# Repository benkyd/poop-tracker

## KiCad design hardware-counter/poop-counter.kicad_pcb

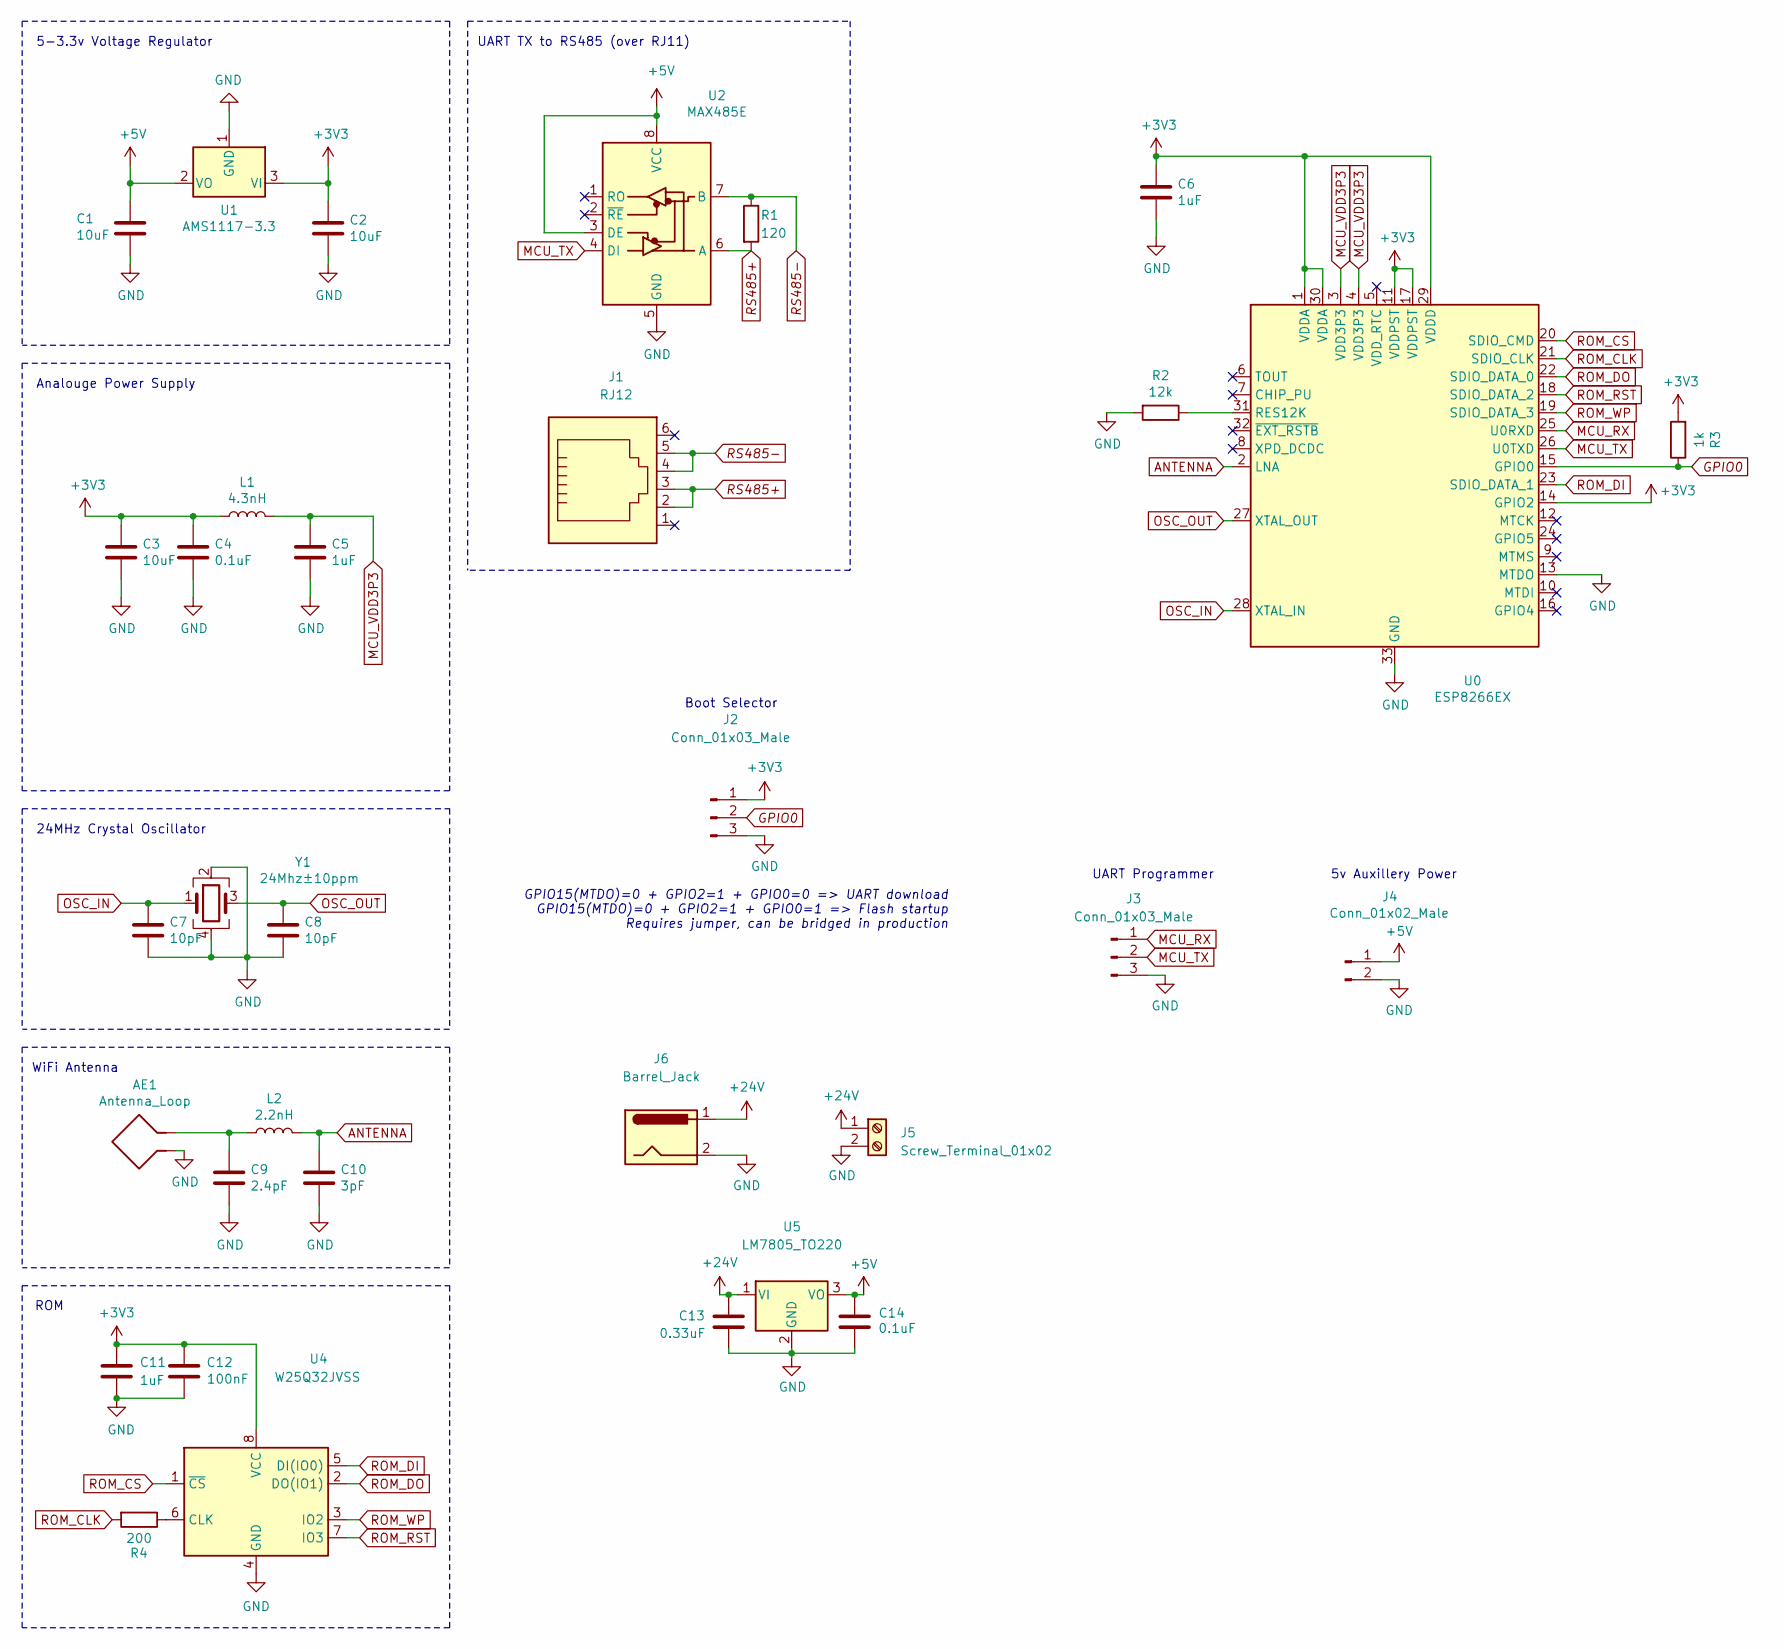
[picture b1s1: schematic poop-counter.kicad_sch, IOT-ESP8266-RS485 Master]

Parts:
AE1: Antenna_Loop; Texas_SWRA117D_2.4GHz_Right
C1, C2, C3: 10uF; C_0805_2012Metric_Pad1.18x1.45mm_HandSolder
C4, C14: 0.1uF; C_0805_2012Metric_Pad1.18x1.45mm_HandSolder
C5, C6, C11: 1uF; C_0805_2012Metric_Pad1.18x1.45mm_HandSolder
C7, C8: 10pF; C_0805_2012Metric_Pad1.18x1.45mm_HandSolder
C9: 2.4pF; C_0805_2012Metric_Pad1.18x1.45mm_HandSolder
C10: 3pF; C_0805_2012Metric_Pad1.18x1.45mm_HandSolder
C12: 100nF; C_0805_2012Metric_Pad1.18x1.45mm_HandSolder
C13: 0.33uF; C_0805_2012Metric_Pad1.18x1.45mm_HandSolder
J1: RJ12; RJ12_Amphenol_54601
J2, J3: Conn_01x03_Male; PinHeader_1x03_P2.54mm_Vertical
J4: Conn_01x02_Male; PinHeader_1x02_P2.54mm_Vertical
J5: Screw_Terminal_01x02; TerminalBlock_bornier-2_P5.08mm
J6: Barrel_Jack; BarrelJack_CLIFF_FC681465S_SMT_Horizontal
L1: 4.3nH; L_0805_2012Metric_Pad1.05x1.20mm_HandSolder
L2: 2.2nH; L_0805_2012Metric_Pad1.05x1.20mm_HandSolder
R1: 120; R_0805_2012Metric_Pad1.20x1.40mm_HandSolder
R2: 12k; R_0805_2012Metric_Pad1.20x1.40mm_HandSolder
R3: 1k; R_0805_2012Metric_Pad1.20x1.40mm_HandSolder
R4: 200; R_0805_2012Metric_Pad1.20x1.40mm_HandSolder
U0: ESP8266EX; QFN-32-1EP_5x5mm_P0.5mm_EP3.45x3.45mm
U1: AMS1117-3.3; SOT-223-3_TabPin2
U2: MAX485E; SOIC127P600X175-8N
U4: W25Q32JVSS; SOIC-8_5.23x5.23mm_P1.27mm
U5: LM7805_TO220; TO-220-3_Vertical
Y1: 24Mhz±10ppm; Crystal_SMD_EuroQuartz_X22-4Pin_2.5x2.0mm

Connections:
+3V3: C2.1, C3.1, C4.1, C6.1, C11.1, C12.1, J2.1, L1.1, R3.2, U0.1 (VDDA), U0.11 (VDDPST), U0.14 (GPIO2), U0.17 (VDDPST), U0.29 (VDDD), U0.30 (VDDA), U1.3 (VI), U4.8 (VCC)
+5V: C1.2, C14.1, J4.1, U1.2 (VO), U2.3 (DE), U2.8 (VCC), U5.3 (VO)
+24V: C13.2, J5.1, J6.1, U5.1 (VI)
ANTENNA: C10.1, L2.2, U0.2 (LNA)
GND: AE1.1, C1.1, C2.2, C3.2, C4.2, C5.2, C6.2, C7.2, C8.2, C9.2, C10.2, C11.2, C12.2, C13.1, C14.2, J2.3, J3.3, J4.2, J5.2, J6.2, R2.2, U0.13 (MTDO), U0.33 (GND), U1.1 (GND), U2.5 (GND), U4.4 (GND), U5.2 (GND), Y1.2, Y1.4
GPIO0: J2.2, R3.1, U0.15 (GPIO0)
MCU_RX: J3.1, U0.25 (U0RXD)
MCU_TX: J3.2, U0.26 (U0TXD), U2.4 (DI)
MCU_VDD3P3: C5.1, L1.2, U0.3 (VDD3P3), U0.4 (VDD3P3)
unnamed: AE1.2, C9.1, L2.1
unnamed: R2.1, U0.31 (RES12K)
unnamed: R4.1, U4.6 (CLK)
OSC_IN: C7.1, U0.28 (XTAL_IN), Y1.1
OSC_OUT: C8.1, U0.27 (XTAL_OUT), Y1.3
ROM_CLK: R4.2, U0.21 (SDIO_CLK)
ROM_CS: U0.20 (SDIO_CMD), U4.1 (~CS)
ROM_DI: U0.23 (SDIO_DATA_1), U4.5 (DI(IO0))
ROM_DO: U0.22 (SDIO_DATA_0), U4.2 (DO(IO1))
ROM_RST: U0.18 (SDIO_DATA_2), U4.7 (IO3)
ROM_WP: U0.19 (SDIO_DATA_3), U4.3 (IO2)
RS485+: J1.2, J1.3, R1.2, U2.6 (A)
RS485-: J1.4, J1.5, R1.1, U2.7 (B)
no_connect_23: J1.1
no_connect_24: J1.6
no_connect_25: U0.10 (MTDI)
no_connect_26: U0.12 (MTCK)
no_connect_27: U0.16 (GPIO4)
no_connect_28: U0.24 (GPIO5)
no_connect_29: U0.32 (~EXT_RSTB~)
no_connect_30: U0.5 (VDD_RTC)
no_connect_31: U0.6 (TOUT)
no_connect_32: U0.7 (CHIP_PU)
no_connect_33: U0.8 (XPD_DCDC)
no_connect_34: U0.9 (MTMS)
no_connect_35: U2.1 (RO)
no_connect_36: U2.2 (~RE)

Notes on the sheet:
WiFi Antenna
ROM
5-3.3v Voltage Regulator
Analouge Power Supply
24MHz Crystal Oscillator
UART TX to RS485 (over RJ11)
Boot Selector
GPIO15(MTDO)=0 + GPIO2=1 + GPIO0=0 => UART download GPIO15(MTDO)=0 + GPIO2=1 + GPIO0=1 => Flash startup Requires jumper, can be bridged in production
UART Programmer
5v Auxillery Power

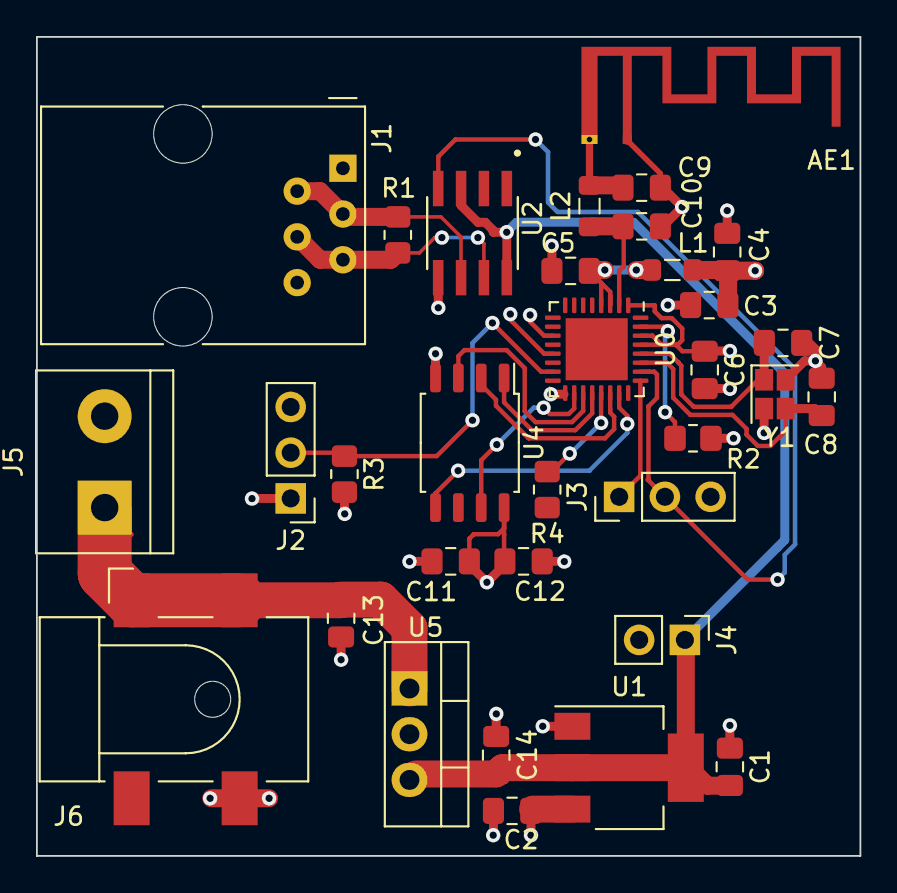
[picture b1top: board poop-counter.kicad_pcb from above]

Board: 4 copper layers, 45.8 x 45.5 mm, 33 parts (0 on the bottom side), 22 nets.

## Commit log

2021-07-18 started component gathering
2021-07-19 voltage regulation and decoupling for mcu
2021-07-19 changes ennit
2021-07-31 USBC!
2021-07-31 removed backups
2021-07-31 finish PCB schem
2021-07-31 footprint moment
2021-07-31 changes people changes
2021-08-01 bout to remove USB
2021-08-01 done v1, need to redo routing entirely lol
2021-08-26 FLIPDOT FIRMWAREEEE
2021-12-21 PooTracker App
2021-12-23 i dont know react very well and it shows
